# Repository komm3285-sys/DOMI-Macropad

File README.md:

# DOMI-Macropad
my macropad with 15 keys and a roatry encoder built with the seed studio rp2040

pcb:

schematic:

Bill of Materials:
1x unsoldered Seeed XIAO RP2040
16x through-hole 1N4148 Diodes
15 MX-Style switches
1x EC11 Rotary encoders
15x white blank DSA keycaps
15x SK6812 MINI-E LEDs
4x M3x16mm screws
4x M3x5mx4mm heatset inserts

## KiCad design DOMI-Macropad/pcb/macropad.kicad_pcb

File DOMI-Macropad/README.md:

# DOMI-Macropad
my macropad with 15 keys and a roatry encoder built with the seed studio rp2040

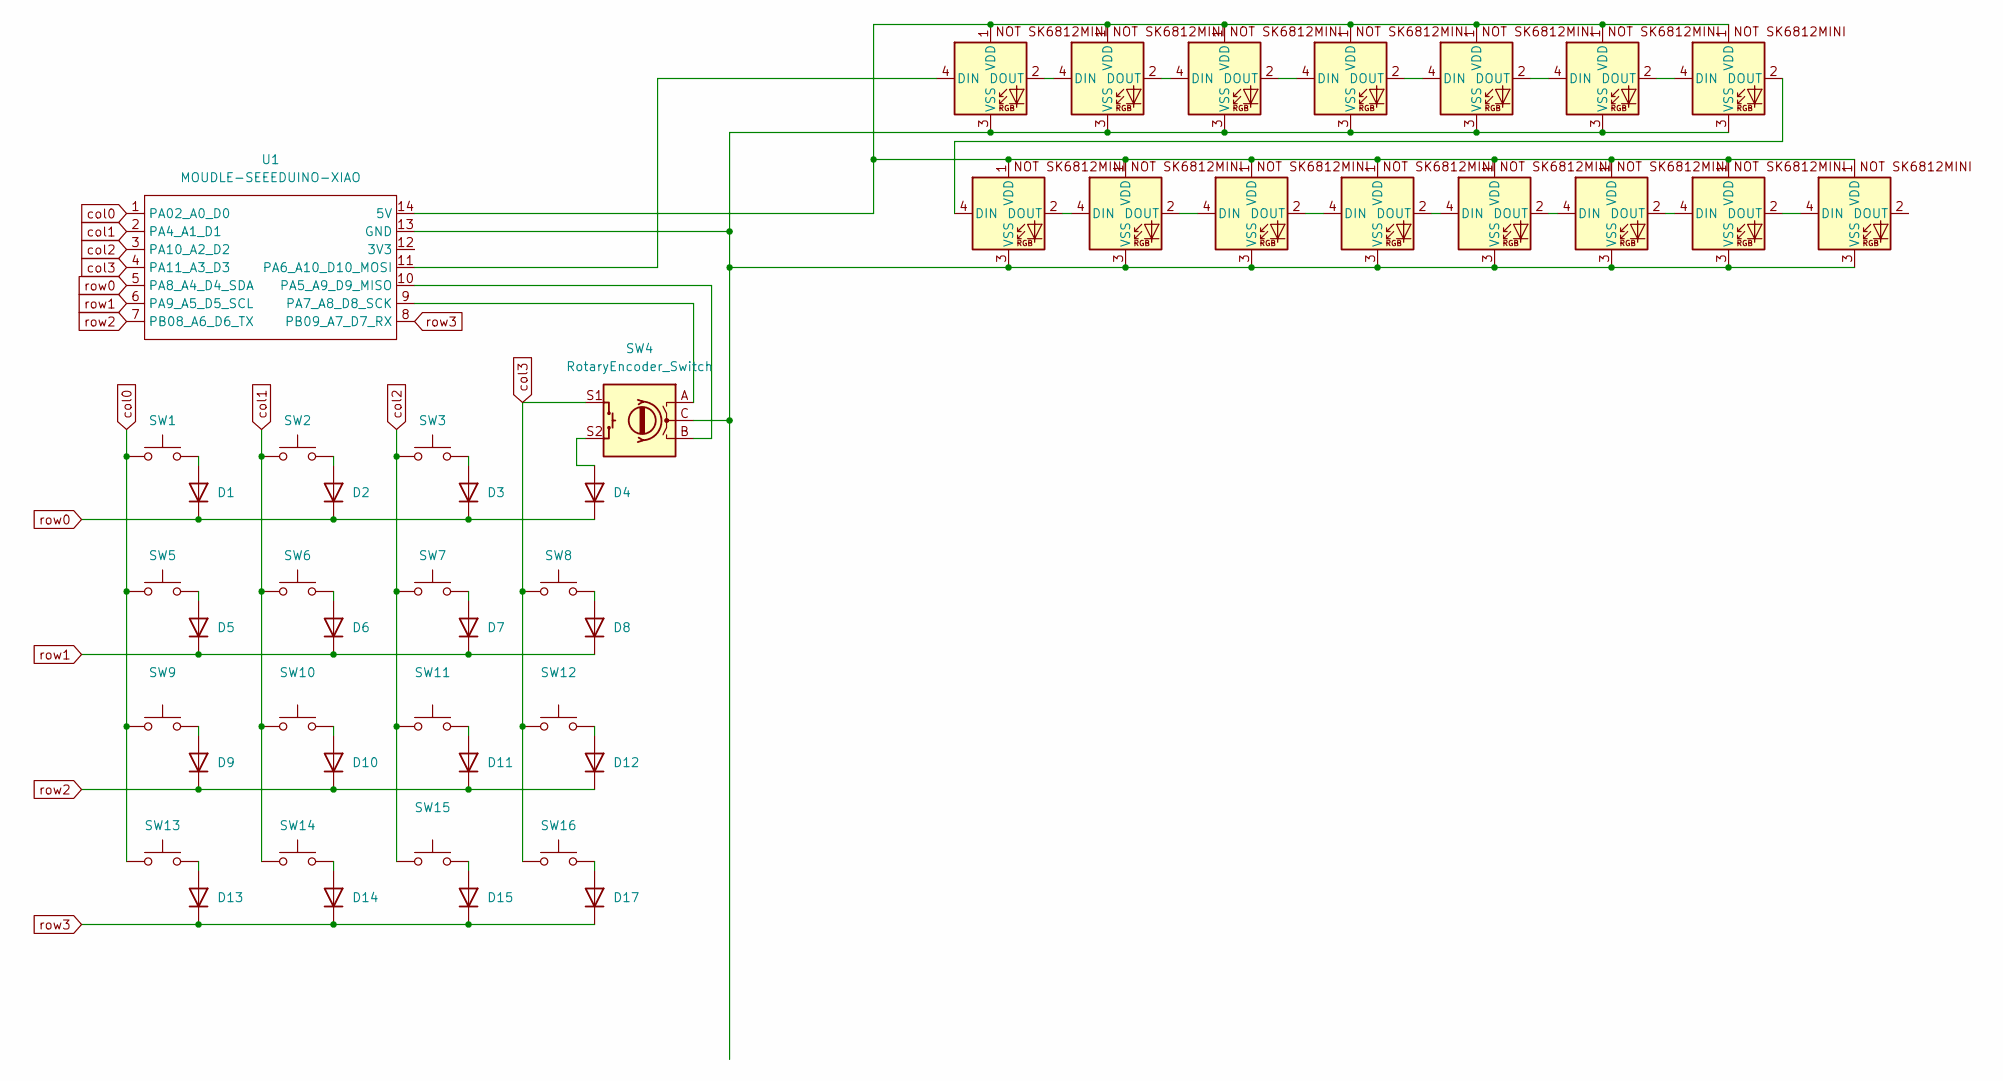
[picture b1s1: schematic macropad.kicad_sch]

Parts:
D1, D2, D3, D4, D5, D6, D7, D8, D9, D10, D11, D12, D13, D14, D15, D17: 1N4148; D_DO-35_SOD27_P7.62mm_Horizontal
D16, D18, D19, D20, D21, D22, D23, D24, D25, D26, D27, D28, D29, D30, D31: SK6812MINI-E; SK6812MINI-E_fixed
SW1, SW2, SW3, SW5, SW6, SW7, SW8, SW9, SW10, SW11, SW12, SW13, SW14, SW15, SW16: SW_Push; MXOnly-1U-NoLED
SW4: RotaryEncoder_Switch; RotaryEncoder_Alps_EC11E-Switch_Vertical_H20mm
U1: MOUDLE-SEEEDUINO-XIAO; XIAO-Generic-Hybrid-14P-2.54-21X17.8MM

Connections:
unnamed: D1.2 (A), SW1.2
unnamed: D2.2 (A), SW2.2
unnamed: D3.2 (A), SW3.2
unnamed: D4.2 (A), SW4.S2
unnamed: D5.2 (A), SW5.2
unnamed: D6.2 (A), SW6.2
unnamed: D7.2 (A), SW7.2
unnamed: D8.2 (A), SW8.2
unnamed: D9.2 (A), SW9.2
unnamed: D10.2 (A), SW10.2
unnamed: D11.2 (A), SW11.2
unnamed: D12.2 (A), SW12.2
unnamed: D13.2 (A), SW13.2
unnamed: D14.2 (A), SW14.2
unnamed: D15.2 (A), SW15.2
unnamed: D16.4 (DIN), D18.2 (DOUT)
unnamed: D16.2 (DOUT), D29.4 (DIN)
unnamed: D16.1 (VDD), D18.1 (VDD), D19.1 (VDD), D20.1 (VDD), D21.1 (VDD), D22.1 (VDD), D23.1 (VDD), D24.1 (VDD), D25.1 (VDD), D26.1 (VDD), D27.1 (VDD), D28.1 (VDD), D29.1 (VDD), D30.1 (VDD), D31.1 (VDD), U1.14 (5V)
unnamed: D16.3 (VSS), D18.3 (VSS), D19.3 (VSS), D20.3 (VSS), D21.3 (VSS), D22.3 (VSS), D23.3 (VSS), D24.3 (VSS), D25.3 (VSS), D26.3 (VSS), D27.3 (VSS), D28.3 (VSS), D29.3 (VSS), D30.3 (VSS), D31.3 (VSS), SW4.C, U1.13 (GND)
unnamed: D17.2 (A), SW16.2
unnamed: D18.4 (DIN), D19.2 (DOUT)
unnamed: D19.4 (DIN), U1.11 (PA6_A10_D10_MOSI)
unnamed: D20.4 (DIN), D21.2 (DOUT)
unnamed: D20.2 (DOUT), D30.4 (DIN)
unnamed: D21.4 (DIN), D29.2 (DOUT)
unnamed: D22.4 (DIN), D24.2 (DOUT)
unnamed: D22.2 (DOUT), D28.4 (DIN)
unnamed: D23.4 (DIN), D28.2 (DOUT)
unnamed: D23.2 (DOUT), D27.4 (DIN)
unnamed: D24.4 (DIN), D31.2 (DOUT)
unnamed: D25.4 (DIN), D26.2 (DOUT)
unnamed: D26.4 (DIN), D27.2 (DOUT)
unnamed: D30.2 (DOUT), D31.4 (DIN)
unnamed: SW4.B, U1.10 (PA5_A9_D9_MISO)
unnamed: SW4.A, U1.9 (PA7_A8_D8_SCK)
col0: SW1.1, SW5.1, SW9.1, SW13.1, U1.1 (PA02_A0_D0)
col1: SW2.1, SW6.1, SW10.1, SW14.1, U1.2 (PA4_A1_D1)
col2: SW3.1, SW7.1, SW11.1, SW15.1, U1.3 (PA10_A2_D2)
col3: SW4.S1, SW8.1, SW12.1, SW16.1, U1.4 (PA11_A3_D3)
row0: D1.1 (K), D2.1 (K), D3.1 (K), D4.1 (K), U1.5 (PA8_A4_D4_SDA)
row1: D5.1 (K), D6.1 (K), D7.1 (K), D8.1 (K), U1.6 (PA9_A5_D5_SCL)
row2: D9.1 (K), D10.1 (K), D11.1 (K), D12.1 (K), U1.7 (PB08_A6_D6_TX)
row3: D13.1 (K), D14.1 (K), D15.1 (K), D17.1 (K), U1.8 (PB09_A7_D7_RX)

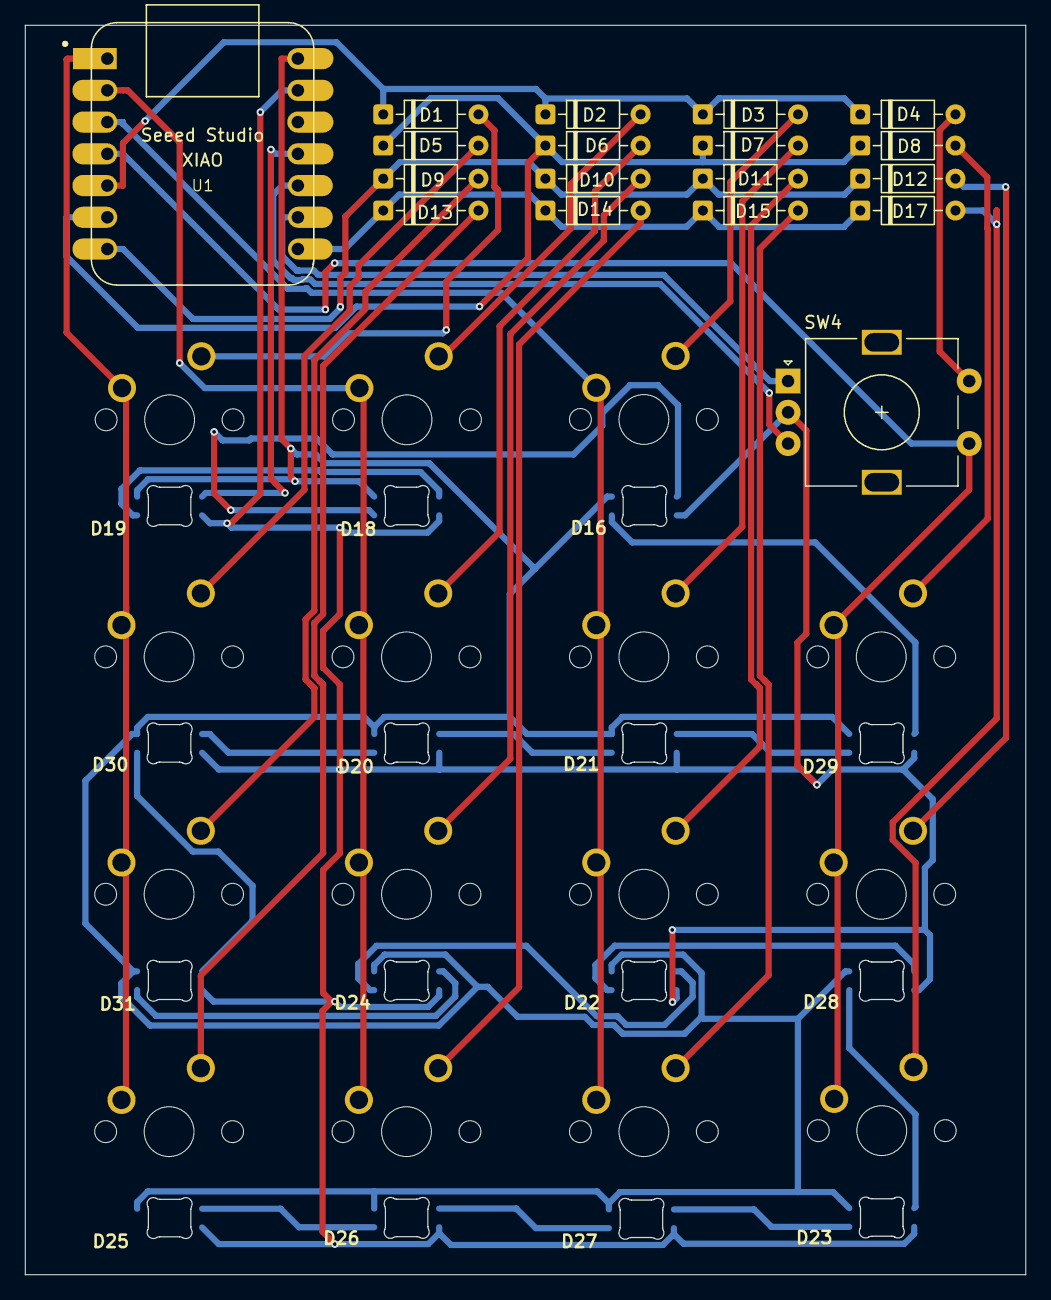
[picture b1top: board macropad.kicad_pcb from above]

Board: 2 copper layers, 80.1 x 100.0 mm, 48 parts (0 on the bottom side), 43 nets.
